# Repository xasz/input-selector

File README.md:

# input-selector

> :warning: THIS IS UNDER CONSTRUCTION

Little project i am trying to do, after building a symasym.

## Goal
An simple but high quality input selector for stereo audio with 8 inputs and 2 outps.
There will be a rotary switch with an oled on the front of the device for the selection of the input and a button for th output selection.
Furthermore there will be a controller with full rest support for controlling the device.

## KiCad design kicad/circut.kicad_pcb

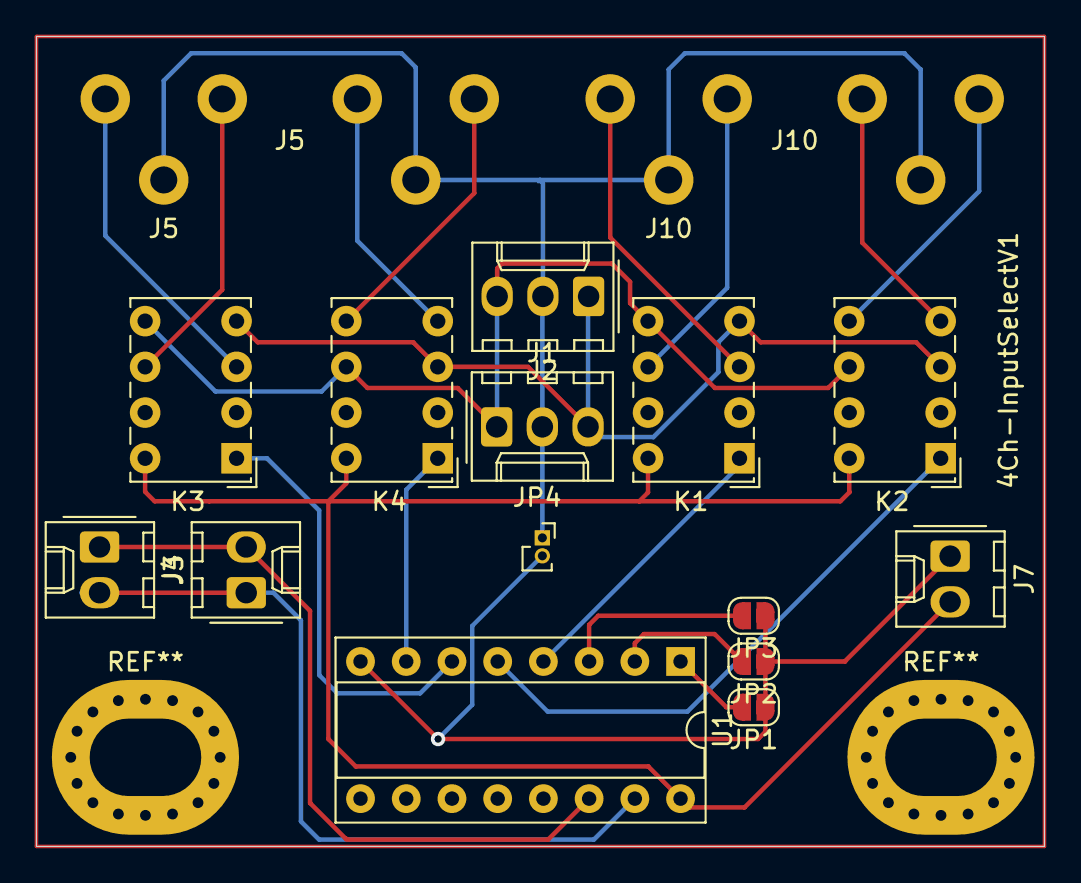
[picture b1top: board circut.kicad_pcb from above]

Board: 2 copper layers, 56.0 x 45.0 mm, 16 parts (0 on the bottom side), 22 nets.

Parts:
J1, J2: AudioOut; Molex_KK-254_AE-6410-03A_1x03_P2.54mm_Vertical
J3, J4: I2C; Molex_KK-254_AE-6410-02A_1x02_P2.54mm_Vertical
J5, J10: Input 1/2; cinch_2X2_Vertical
J7: VDD 5v; Molex_KK-254_AE-6410-02A_1x02_P2.54mm_Vertical
JP1: A0; SolderJumper-2_P1.3mm_Open_RoundedPad1.0x1.5mm
JP2: A1; SolderJumper-2_P1.3mm_Open_RoundedPad1.0x1.5mm
JP3: A2; SolderJumper-2_P1.3mm_Open_RoundedPad1.0x1.5mm
JP4: Audio to Control GND; PinSocket_1x02_P1.00mm_Vertical
K1, K2, K3, K4: G6K-2; Relay_DPDT_Omron_G6K-2P
U1: PCF8574; DIP-16_W7.62mm_Socket

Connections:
GND: J7.1, JP1.1 (A), JP2.1 (A), JP3.1 (A), JP4.2 (B), U1.8 (VSS)
GND1: J1.2, J2.2, J5.3 (EXT), J5.6 (EXT), J10.3 (EXT), J10.6 (EXT), JP4.1 (A)
unnamed: J1.1, J2.3, K1.5, K2.6, K3.5, K4.6
unnamed: J1.3, J2.1, K1.4, K2.3, K3.4, K4.3
unnamed: J3.1, J4.2, U1.14 (SCL)
unnamed: J3.2, J4.1, U1.15 (SDA)
unnamed: J5.1 (IN1), K3.6
unnamed: J5.2 (IN2), K3.3
unnamed: J5.4 (IN1), K4.5
unnamed: J5.5 (IN2), K4.4
unnamed: J10.1 (IN1), K1.6
unnamed: J10.2 (IN2), K1.3
unnamed: J10.4 (IN1), K2.5
unnamed: J10.5 (IN2), K2.4
unnamed: JP1.2 (B), U1.1 (A0)
unnamed: JP2.2 (B), U1.2 (A1)
unnamed: JP3.2 (B), U1.3 (A2)
unnamed: K1.1, U1.4 (P0)
unnamed: K2.1, U1.5 (P1)
unnamed: K3.1, U1.6 (P2)
unnamed: K4.1, U1.7 (P3)
VDD: J7.2, K1.8, K2.8, K3.8, K4.8, U1.16 (VDD)

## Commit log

2021-12-11 I don't know what i am doing
2021-12-11 Fix some Path
2021-12-12 First full Wireup
2021-12-12 added i2c port extender for the adgs
2021-12-12 hating kicad
2022-02-22 Working with relais
    + first schematic
    + basic pcb layout
    + zip to gitignore
2022-02-27 Added cinch 2x2 symbol and footprint for 1x2 and 2x2
2022-02-27 Second PCB Layout - Much smaller. Changed relais wireing.
